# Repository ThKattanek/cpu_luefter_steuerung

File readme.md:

# CPU-Lüfter Steuerung
Steuerung eines CPU Lüfters per Attiny24a und Anzeige auf 7-Segmentanzeige. Bedienung per Taster.

### [Latest version here](https://github.com/ThKattanek/cpu_luefter_steuerung/releases/latest)

## Bilder

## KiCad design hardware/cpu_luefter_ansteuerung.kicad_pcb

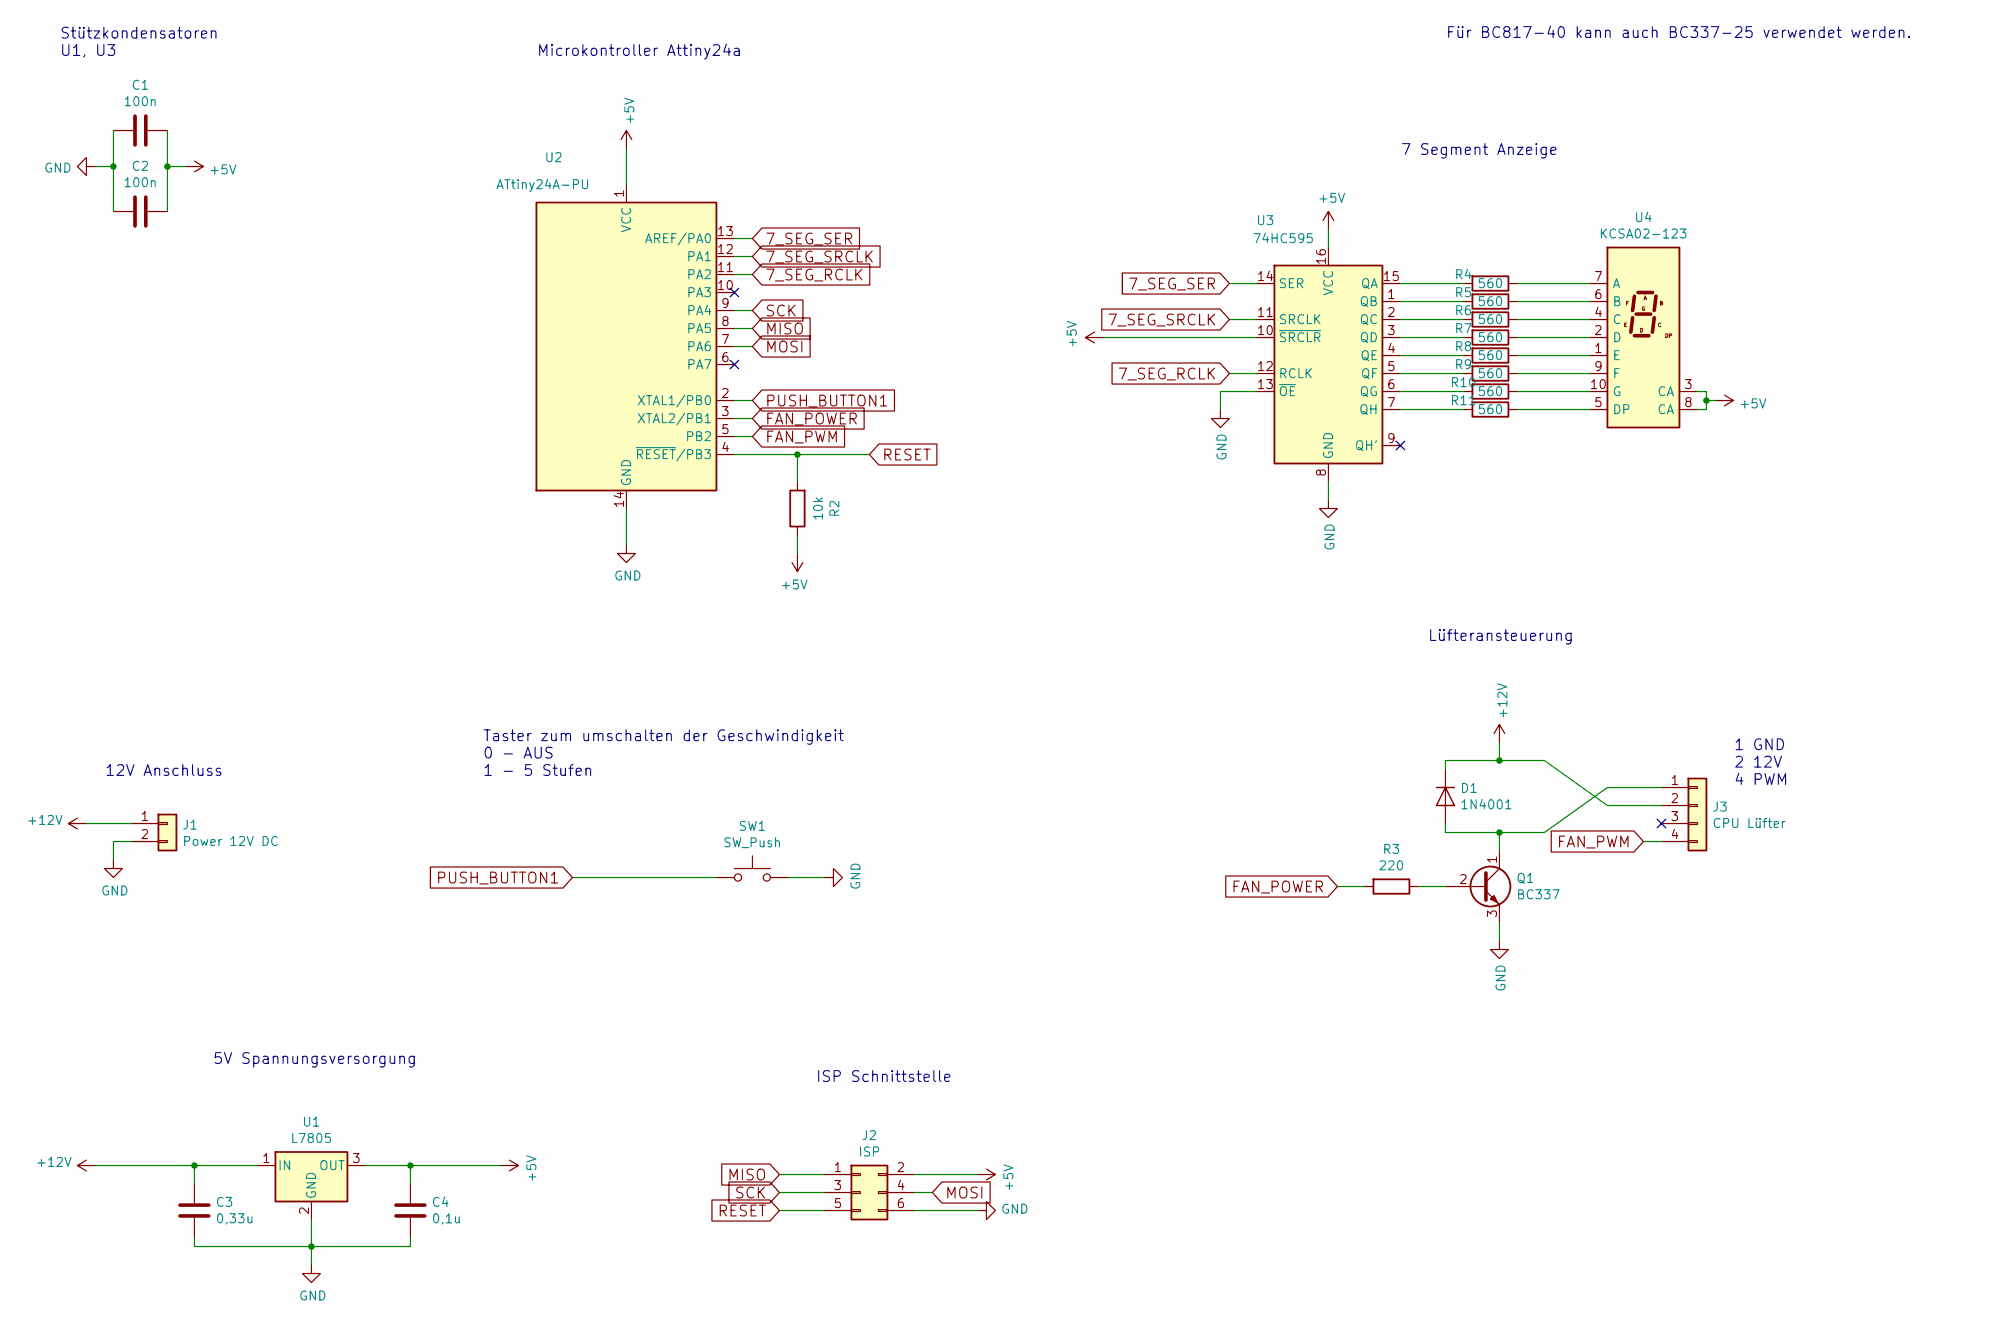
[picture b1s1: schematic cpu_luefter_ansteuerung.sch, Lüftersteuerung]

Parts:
C1, C2: 100n; C_Disc_D5.0mm_W2.5mm_P2.50mm
C3: 0,33u; C_Disc_D5.0mm_W2.5mm_P2.50mm
C4: 0,1u; C_Disc_D5.0mm_W2.5mm_P2.50mm
D1: 1N4001; D_DO-41_SOD81_P10.16mm_Horizontal
J1: Power 12V DC; Molex_KK-254_AE-6410-02A_1x02_P2.54mm_Vertical
J2: ISP; IDC-Header_2x03_P2.54mm_Vertical
J3: CPU Lüfter; PinSocket_1x04_P2.54mm_Vertical
Q1: BC337; TO-92_Inline
R2: 10k; R_Axial_DIN0207_L6.3mm_D2.5mm_P10.16mm_Horizontal
R3: 220; R_Axial_DIN0207_L6.3mm_D2.5mm_P10.16mm_Horizontal
R4, R5, R6, R7, R8, R9, R10, R11: 560; R_Axial_DIN0207_L6.3mm_D2.5mm_P10.16mm_Horizontal
SW1: SW_Push; SW_PUSH_6mm_H5mm
U1: L7805; TO-220-3_Horizontal_TabDown
U2: ATtiny24A-PU; DIP-14_W7.62mm
U3: 74HC595; DIP-16_W7.62mm_LongPads
U4: KCSA02-123; HDSP-7801

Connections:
7_SEG_RCLK: U2.11 (PA2), U3.12 (RCLK)
7_SEG_SER: U2.13 (AREF/PA0), U3.14 (SER)
7_SEG_SRCLK: U2.12 (PA1), U3.11 (SRCLK)
+5V: C1.1, C2.1, C4.1, J2.2, R2.1, U1.3 (OUT), U2.1 (VCC), U3.10 (~SRCLR), U3.16 (VCC), U4.3 (CA), U4.8 (CA)
+12V: C3.1, D1.1 (K), J1.1, J3.2, U1.1 (IN)
FAN_POWER: R3.2, U2.3 (XTAL2/PB1)
FAN_PWM: J3.4, U2.5 (PB2)
GND: C1.2, C2.2, C3.2, C4.2, J1.2, J2.6, Q1.3 (E), SW1.2, U1.2 (GND), U2.14 (GND), U3.8 (GND), U3.13 (~OE)
MISO: J2.1, U2.8 (PA5)
MOSI: J2.4, U2.7 (PA6)
unnamed: D1.2 (A), J3.1, Q1.1 (C)
unnamed: Q1.2 (B), R3.1
unnamed: R4.1, U4.7 (A)
unnamed: R4.2, U3.15 (QA)
unnamed: R5.1, U4.6 (B)
unnamed: R5.2, U3.1 (QB)
unnamed: R6.1, U4.4 (C)
unnamed: R6.2, U3.2 (QC)
unnamed: R7.1, U4.2 (D)
unnamed: R7.2, U3.3 (QD)
unnamed: R8.1, U4.1 (E)
unnamed: R8.2, U3.4 (QE)
unnamed: R9.1, U4.9 (F)
unnamed: R9.2, U3.5 (QF)
unnamed: R10.1, U4.10 (G)
unnamed: R10.2, U3.6 (QG)
unnamed: R11.1, U4.5 (DP)
unnamed: R11.2, U3.7 (QH)
PUSH_BUTTON1: SW1.1, U2.2 (XTAL1/PB0)
RESET: J2.5, R2.2, U2.4 (~RESET~/PB3)
SCK: J2.3, U2.9 (PA4)

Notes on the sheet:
Für BC817-40 kann auch BC337-25 verwendet werden.
5V Spannungsversorgung
12V Anschluss
Taster zum umschalten der Geschwindigkeit 0 - AUS 1 - 5 Stufen
1 GND 2 12V 4 PWM
Stützkondensatoren U1, U3
ISP Schnittstelle
Microkontroller Attiny24a
7 Segment Anzeige
Lüfteransteuerung

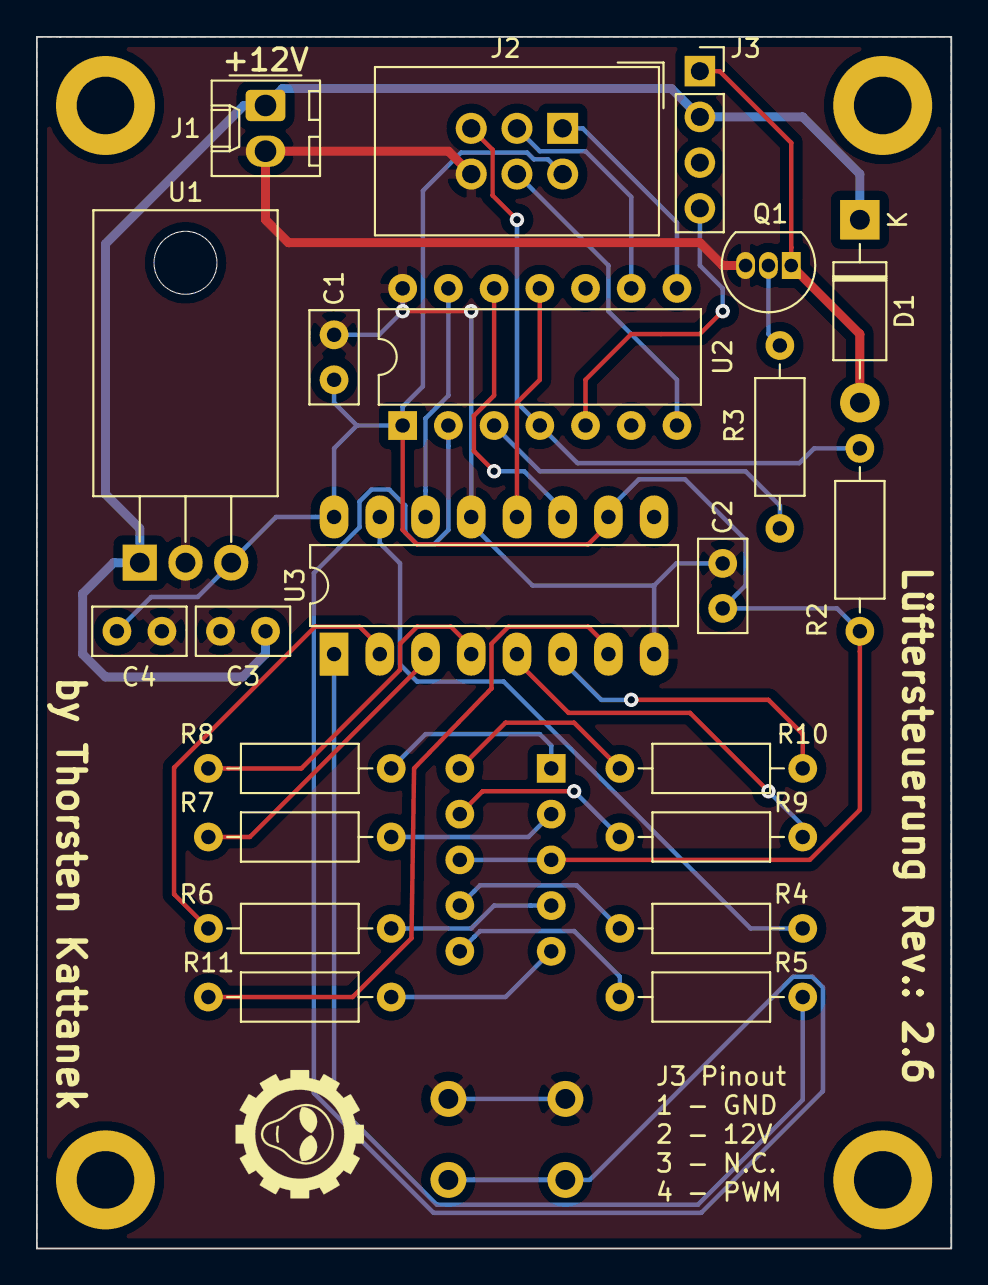
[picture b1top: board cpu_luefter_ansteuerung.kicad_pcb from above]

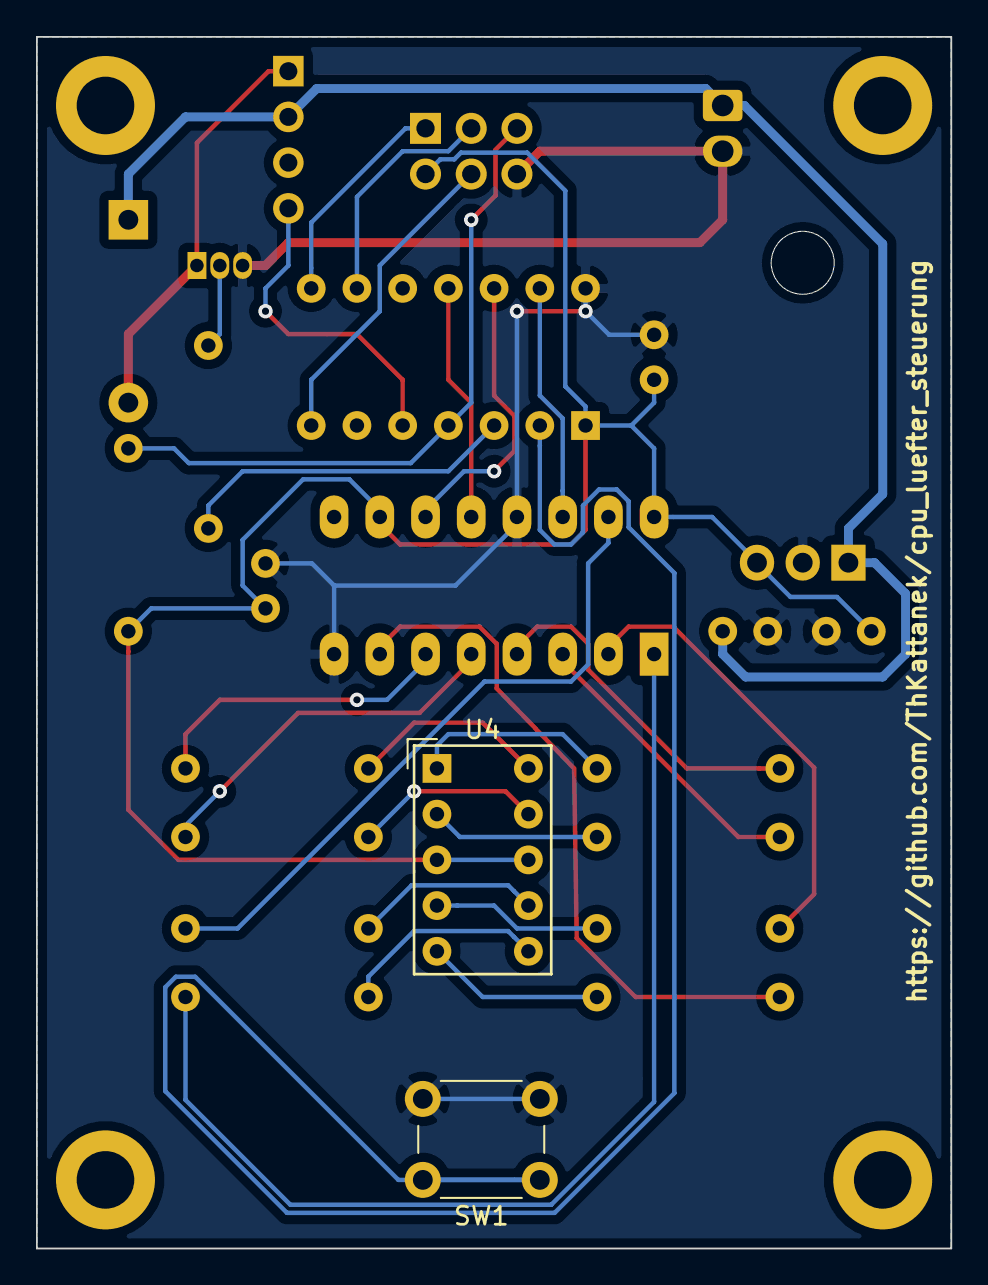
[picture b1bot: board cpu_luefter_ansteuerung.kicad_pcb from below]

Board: 2 copper layers, 50.8 x 67.3 mm, 24 parts (2 on the bottom side), 31 nets.

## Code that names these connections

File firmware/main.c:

/* Name: main.c
 * Projekt: cpu_lueftersteuerung
 * Author: Thorsten Kattanek
 * Geändert am: 19.05.2019
 * Copyright: Thorsten Kattanek
 * License: GNU GPL v2 (see License.txt), GNU GPL v3 or proprietary (CommercialLicense.txt)
 *
 */

#define F_CPU   8000000UL
    
#include <avr/io.h>
#include <avr/wdt.h>
#include <avr/interrupt.h>
#include <util/delay.h>
#include <avr/pgmspace.h>   /* benötigt von usbdrv.h */

// PinOut
// PB1 - FAN_POWER
// PB2 - FAN_PWM

// PA0 - 7_SEG_SER
// PA1 - 7_SEG_SRCLK
// PA2 - 7_SEG_RCLK

// PB0 - PUSH_BUTTON1

void InitMotor(void);
void InitPWMChannel(void);
void Init7Segment(void);
void InitInputs(void);

void MotorOn(void);
void MotorOff(void);
void SetMotorSpeed(unsigned char speed);

void Set7Segment(uint8_t value);
void Set7SegmentNumber(uint8_t num);

int main(void)
{
    InitMotor();
    InitPWMChannel();
    Init7Segment();
    InitInputs();

    Set7SegmentNumber(0);

    uint8_t number = 0;

    const uint8_t speed_tbl[6] = {0,50,100,150,200,255};
    uint8_t current_speed = 0; 	// 0 = Aus
    uint8_t key, old_key = 0;
    uint8_t key_wait1 = 0;

    while(1)
    {
        key = (PINB >> PB0) & 1;

        if(key != old_key && key_wait1 == 0)
        {
            if(!key)
            {
                current_speed++;
                if(current_speed == 6)
                    current_speed = 0;
                Set7SegmentNumber(current_speed);

                if(current_speed == 0)
                    MotorOff();
                else
                    MotorOn();

                SetMotorSpeed(speed_tbl[current_speed]);
            }
            key_wait1 = 0xff;
        }
        else if(key_wait1 > 0) {
            key_wait1--;
        }

        old_key = key;
    }
}

/* ------------------------------------------------------------------------- */

void InitMotor(void)
{
    // Motor On/Off Signal muss definiert 5V oder GND haben.
    DDRB |= 1 << PB1;
    PORTB &= ~(1 << PB1);
}

void InitPWMChannel(void)
{
    DDRB |= 1 << PB2;                                   // OC0A auf Ausgang setzen
    TCCR0A |= 1 << COM0A1 | 1 << WGM00 | 1 << WGM01;     // OC0A non-invertmode - FAST PWM Mode
    TCCR0B |= 1 << CS01;                                 // Prescaler auf 8 --> 8MHz / 8 / 256 = 3,9 KHz
    OCR0A = 0;
}

void Init7Segment(void)
{
    DDRA |= 1 << PA0 | 1 << PA1 | 1 << PA2;

    PORTA |= 1 << PA0;       // SER auf HI -> LED AUS

    PORTA &= ~(1 << PA1 | 1 << PA2);    // SRCLK & RCLK auf Low setzen

    for(int i=0; i<8; i++)      // SRCLK 8x
    {
        PORTA |= 1 << PA1;
        PORTA &= ~(1 << PA1);
    }

    PORTA |= 1 << PA2;      // RCLK 1x
    PORTA &= ~(1 << PA2);
}

void InitInputs(void)
{
    DDRB &= ~(1 << PB0);
    PINB |= 1 << PB0;      // Set intern pullups
}

void Set7Segment(uint8_t value)
{
    for(int i=0; i<8; i++)
    {
        PORTA &= 0xfe;                      // SER loeschen
        PORTA |= (value >> (7-i)) & 0x01;   // SER mit Bit füllen
        PORTA ^= 0x01;                      // SER invertieren

        PORTA |= 1 << PA1;                  // SRCLK
        PORTA &= ~(1 << PA1);
    }

    PORTA |= 1 << PA2;                      // RCLK 1x
    PORTA &= ~(1 << PA2);
}

void Set7SegmentNumber(uint8_t num)
{
    const uint8_t num_conv_tbl[10] = {0xed, 0x21, 0xf4, 0xf1, 0x39, 0xd9, 0xdd, 0x61, 0xfd, 0xf9};

    if(num < 10)
    Set7Segment(num_conv_tbl[num]);
}

///
/// \brief MotorOn
///
void MotorOn(void)
{
    PORTB |= 1 << PB1;
}

///
/// \brief MotorOff
///
void MotorOff(void)
{
    PORTB &= ~(1 << PB1);
}

///
/// \brief SetMotorSpeed
/// \param speed = 0-255 (0=slow 255=fast)
///
void SetMotorSpeed(unsigned char speed)
{
    OCR0A = speed;
}

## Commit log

2016-06-19 Unötiges Zeug gelöscht
2019-05-06 Portierung zu KiCad 5.1.2
2019-05-06 Rename README.md to readme.md
2019-05-09 Hardware auf ATiny24A umgestellt und statt 4543 jetzt ein Leistungs Shiftregister für 7Segment ansteuerung.
2019-05-15 Schaltplan etwas optimiert -> Rev: 2.1
2019-05-15 Schaltplan optimiert -> Rev: 2.2 TPIC6B595 durch 74HC595 ersetzt. Alle Bauteile Footprints zugewiesen.
2019-05-15 Angefangen die Firmware an neuen Schaltplan anzupassen.
2019-05-17 Vorwiderstaende fuer 7Segment Anzeige von 150 Ohm auf 560 Ohm geaendert. 74HC595 darf nur gesammt 70mA treiben.
2019-05-17 Fix im Schaltplan.
2019-05-17 7Segment Ausgabe fertig gestellt.
2019-05-19 Firmware fertig gestellt. Push Button auf Internen Pullup gestellt und Soft Entprellung eingesetzt. Spart 1 Kondensator und 1 Widerstand.
2019-05-19 Schaltplan an neuer Firmware angepasst.
2019-05-19 Bilder hinzugefuegt
2019-05-21 pcb angefangen, Bauteile schon mal angeordnet.
2019-05-23 PCB Hand geroutet.
2019-05-23 Display + Taster auf Bottom Layer gelegt. STEP Datei erzeugt.
2019-05-23 PCB habe ich mit meinem Logo versehen und Beschriftet
2019-05-23 Raytrace Bilder hinzugefügt
2019-06-13 PCB - Bestückungsdruck bereinigt
2019-06-13 Gerberfiles erzeugt
2019-06-19 cpu_luefter_ansteuerung_bom.ods ninzugefuegt.
2019-06-20 Shematic und PCB für 7805 korrigiert. Neue Gerber Dateien erzeugt
2019-07-24 J3 Footprint geändert
2019-07-24 Schematic auf Version 2.6 angepasst
2019-07-24 Logo wieder eingefügt
2019-07-24 Gerber Dateien aktuallisiert
2019-07-24 Screenshots geändert.
2019-07-24 Stückliste angepasst
